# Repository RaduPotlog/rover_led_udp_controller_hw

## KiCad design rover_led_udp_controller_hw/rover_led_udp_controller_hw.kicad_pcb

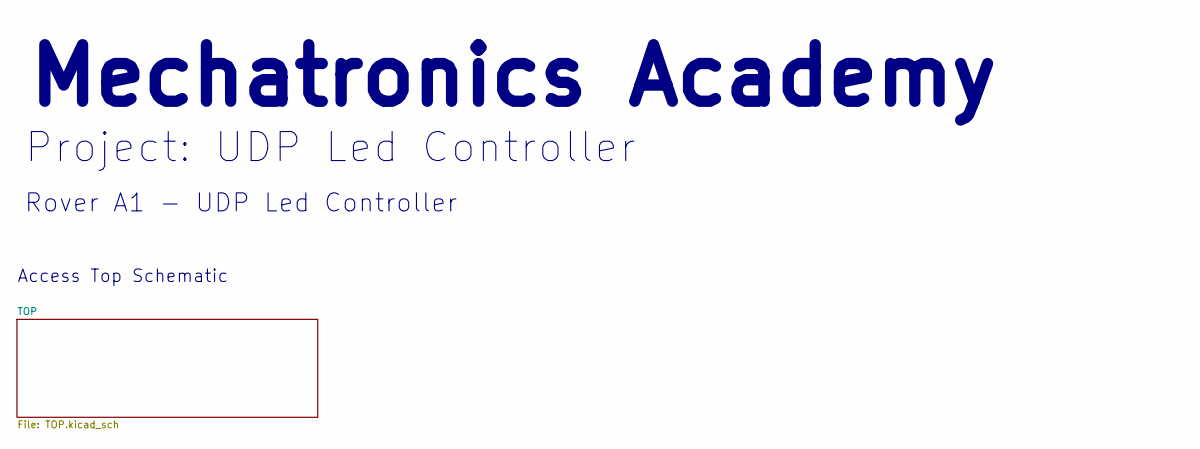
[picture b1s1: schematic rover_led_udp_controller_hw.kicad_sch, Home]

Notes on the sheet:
Rover A1 - UDP Led Controller
Project: UDP Led Controller
Access Top Schematic
Mechatronics Academy

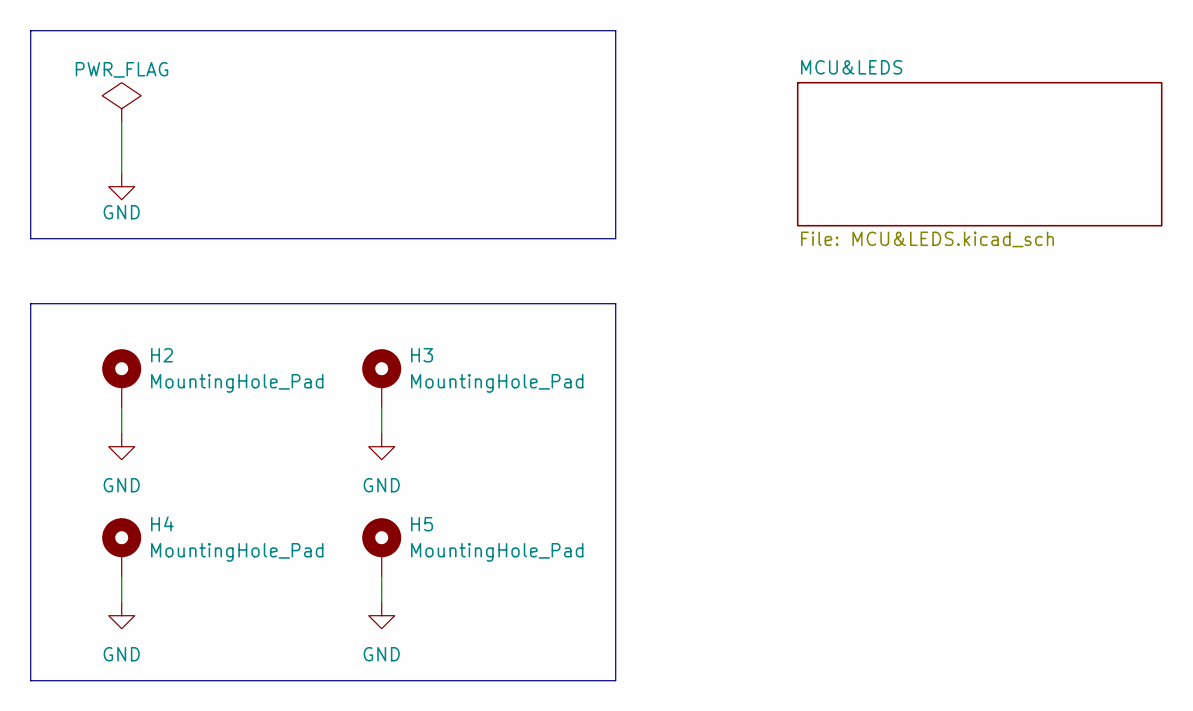
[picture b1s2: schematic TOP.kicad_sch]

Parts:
H2, H3, H4, H5: MountingHole_Pad; MountingHole_2.5mm_Pad_Via

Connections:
GND: H2.1 (1_1), H3.1 (1_1), H4.1 (1_1), H5.1 (1_1); also elsewhere on the board

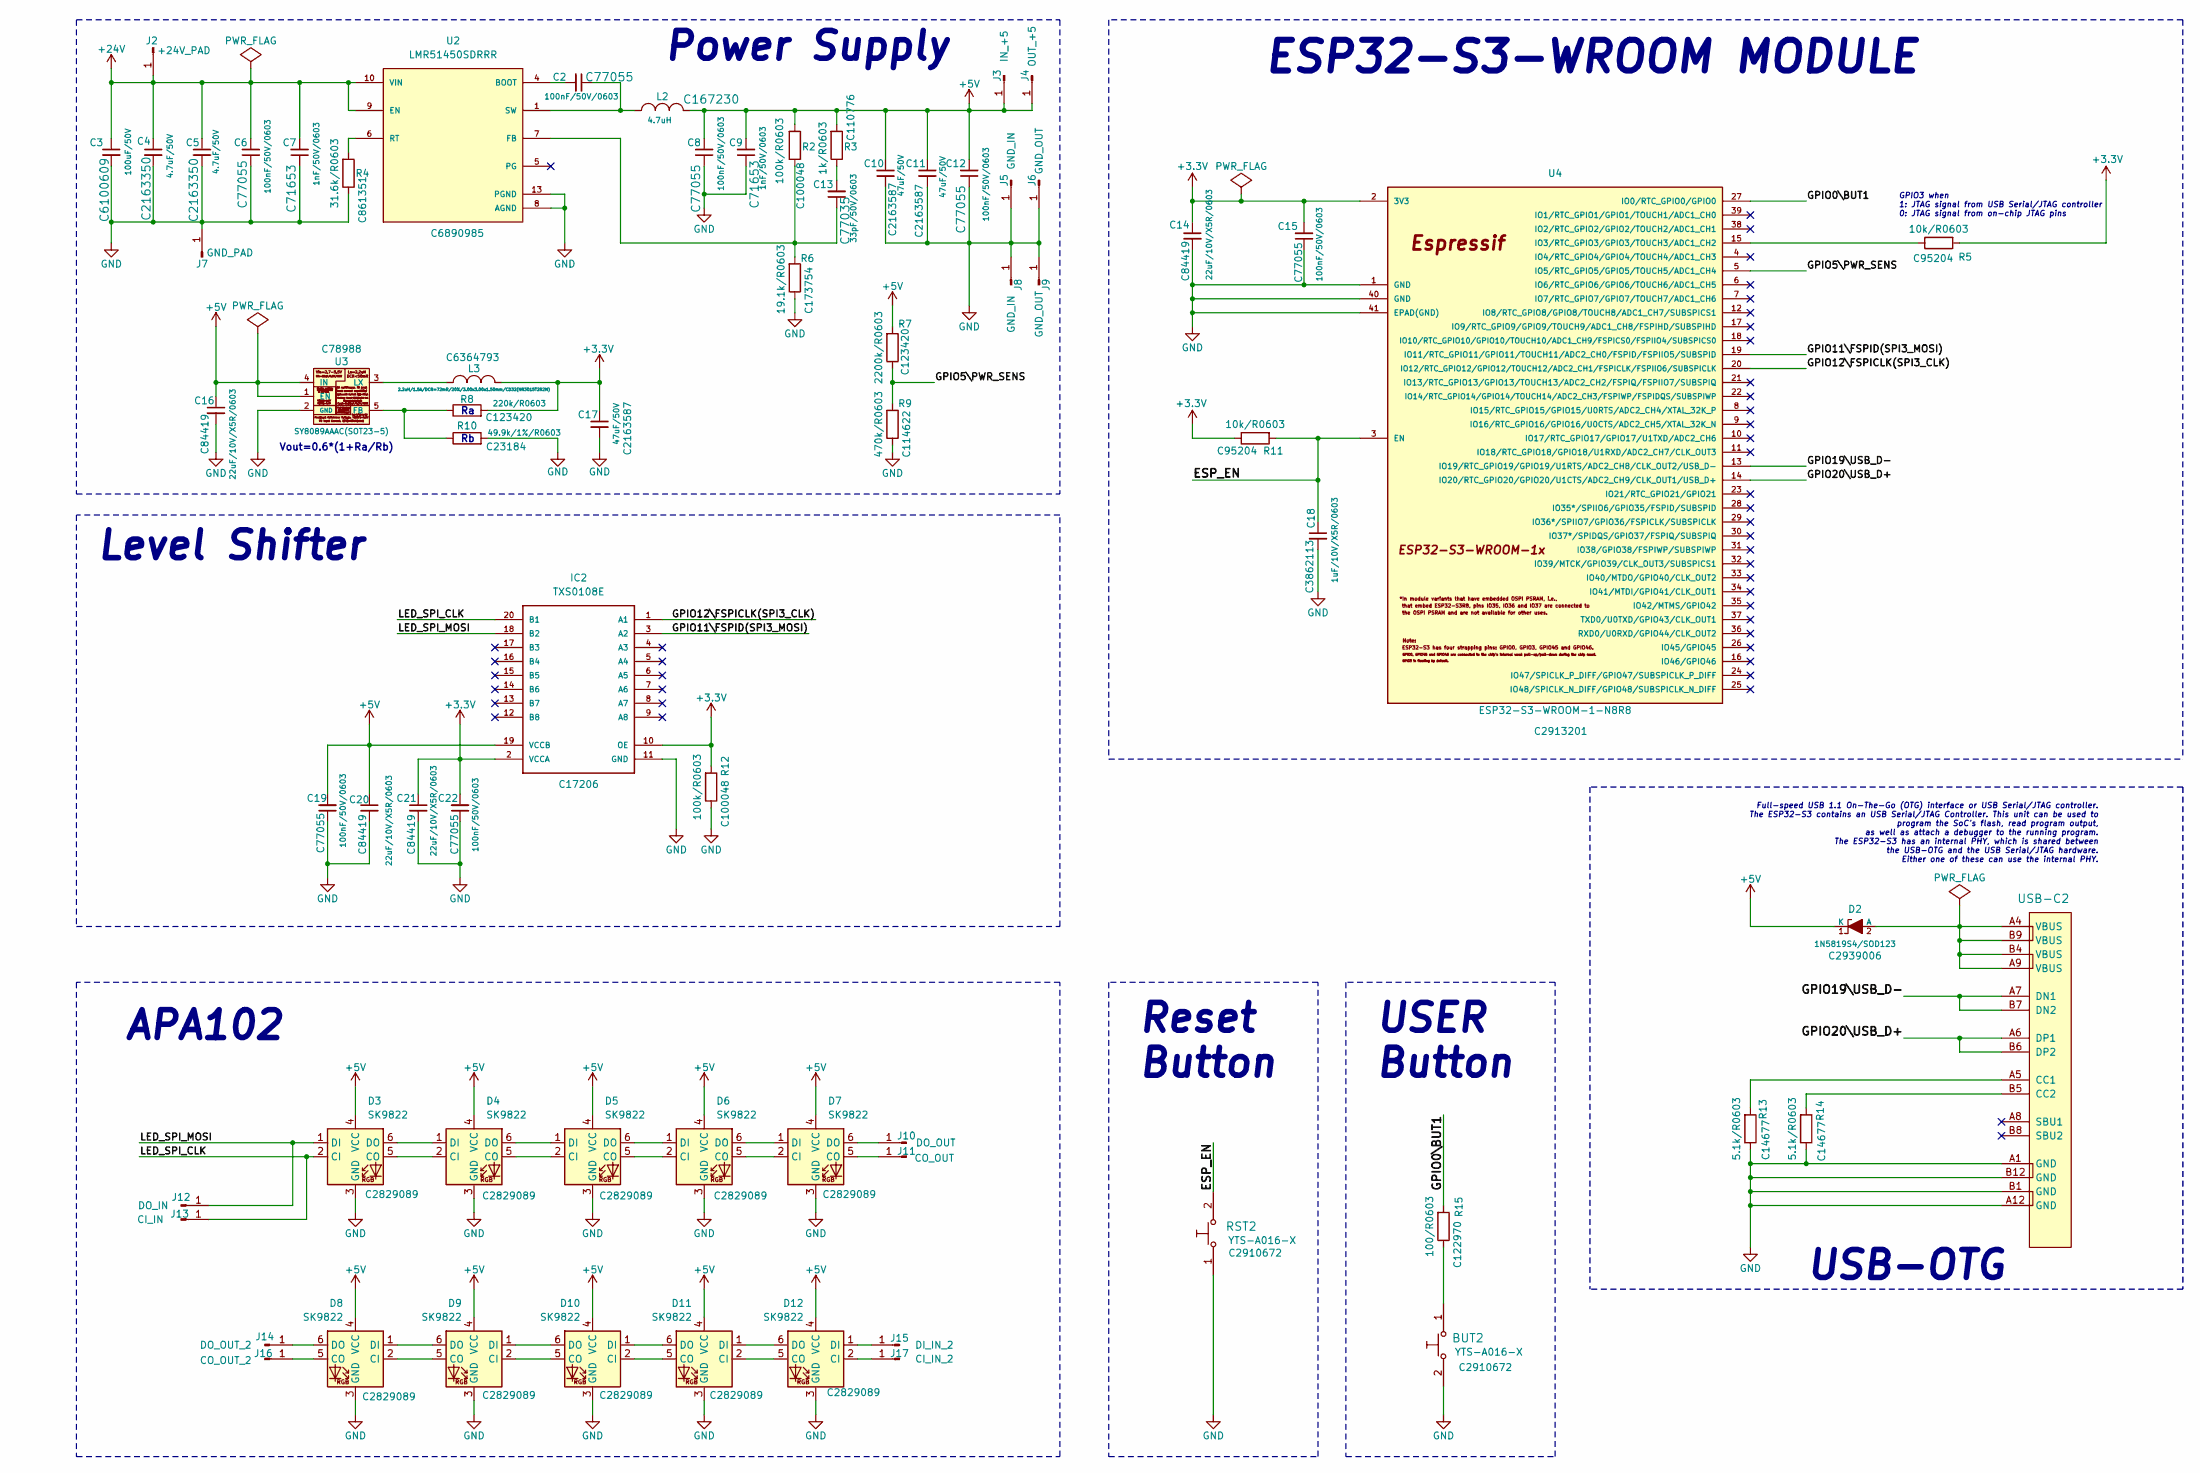
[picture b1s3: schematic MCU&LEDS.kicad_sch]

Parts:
BUT2: YTS-A016-X; JLCPCB C2910672
C2, C6, C8, C12, C15, C19, C22: 100nF/50V/0603; C_0603_1608Metric; JLCPCB C77055
C3: 100uF/50V; CP_Elec_8x10.5; JLCPCB C6100609
C4, C5: 4.7uF/50V; CP_Elec_4x5.7; JLCPCB C2163350
C7, C9: 1nF/50V/0603; C_0603_1608Metric; JLCPCB C71653
C10, C11, C17: 47uF/50V; CP_Elec_6.3x7.7; JLCPCB C2163587
C13: 33pF/50V/0603; C_0603_1608Metric; JLCPCB C77035
C14, C16, C20, C21: 22uF/10V/X5R/0603; C_0603_1608Metric; JLCPCB C84419
C18: 1uF/10V/X5R/0603; C_0603_1608Metric; JLCPCB C3862113
D2: 1N5819S4/SOD123; SOD-123_1C-2A_KA; JLCPCB C2939006
D3, D4, D5, D6, D7, D8, D9, D10, D11, D12: SK9822; LED_RGB_5050-6; JLCPCB C2829089
IC2: TXS0108E; PW_R-PDSO-G20; JLCPCB C17206
J2: +24V_PAD; TestPoint_Pad_1
J3: IN_+5; TestPoint_Pad_1
J4: OUT_+5; TestPoint_Pad_1
J5, J8: GND_IN; TestPoint_Pad_1
J6, J9: GND_OUT; TestPoint_Pad_1
J7: GND_PAD; TestPoint_Pad_1
J10: DO_OUT; TestPoint_Pad
J11: CO_OUT; TestPoint_Pad
J12: DO_IN; TestPoint_Pad
J13: CI_IN; TestPoint_Pad
J14: DO_OUT_2; TestPoint_Pad
J15: DI_IN_2; TestPoint_Pad
J16: CO_OUT_2; TestPoint_Pad
J17: CI_IN_2; TestPoint_Pad
L2: 4.7uH; L_Sunlord_MWSA1003S; JLCPCB C167230
L3: 2.2uH/1.5A/DCR=72mR/20%/3.00x3.00x1.50mm/CD32(NR3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; CD32; JLCPCB C6364793
R2, R12: 100k/R0603; R_0603_1608Metric_Pad0.98x0.95mm_HandSolder; JLCPCB C100048
R3: 1k/R0603; R_0603_1608Metric_Pad0.98x0.95mm_HandSolder; JLCPCB C110776
R4: 31.6k/R0603; R_0603_1608Metric_Pad0.98x0.95mm_HandSolder; JLCPCB C861351
R5, R11: 10k/R0603; R_0603_1608Metric_Pad0.98x0.95mm_HandSolder; JLCPCB C95204
R6: 19.1k/R0603; R_0603_1608Metric_Pad0.98x0.95mm_HandSolder; JLCPCB C173754
R7: 2200k/R0603; R_0603_1608Metric_Pad0.98x0.95mm_HandSolder; JLCPCB C123420
R8: 220k/R0603; R_0603_1608Metric_Pad0.98x0.95mm_HandSolder; JLCPCB C123420
R9: 470k/R0603; R_0603_1608Metric_Pad0.98x0.95mm_HandSolder; JLCPCB C114622
R10: 49.9k/1%/R0603; R_0603_1608Metric_Pad0.98x0.95mm_HandSolder; JLCPCB C23184
R13, R14: 5.1k/R0603; R_0603_1608Metric_Pad0.98x0.95mm_HandSolder; JLCPCB C14677
R15: 100/R0603; R_0603_1608Metric_Pad0.98x0.95mm_HandSolder; JLCPCB C122970
RST2: YTS-A016-X; JLCPCB C2910672
U2: LMR51450SDRRR; PARTREV December 2022; JLCPCB C6890985
U3: SY8089AAAC(SOT23-5); SOT-23-5; JLCPCB C78988
U4: ESP32-S3-WROOM-1-N8R8; ESP32-­S3-­WROOM­-1; JLCPCB C2913201
USB-C2: USB2.0_TYPE-C(A40-00119-A52-12); USB2.0_TYPE-C-ONLY-PADS

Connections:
+3.3V: C14.1, C15.2, C17.1, C21.1, C22.2, IC2.2 (VCCA), IC2.10 (OE), L3.2, R5.2, R8.2, R11.1, R12.2, U4.2 (3V3)
+5V: C8.2, C9.2, C10.1, C11.1, C12.2, C16.1, C19.2, C20.1, D2.1 (K), D3.4 (VCC), D4.4 (VCC), D5.4 (VCC), D6.4 (VCC), D7.4 (VCC), D8.4 (VCC), D9.4 (VCC), D10.4 (VCC), D11.4 (VCC), D12.4 (VCC), IC2.19 (VCCB), J3.1 (Pin_1_1), J4.1 (Pin_1_1), L2.2, R2.2, R3.2, R7.2, U3.1 (EN), U3.4 (IN)
+24V: C3.1, C4.1, C5.1, C6.2, C7.2, J2.1 (Pin_1_1), U2.9 (EN), U2.10 (VIN), U2.11 (VIN), U2.12 (VIN)
/TOP/MCU&LEDS/ESP_EN: C18.1, R11.2, RST2.2, U4.3 (EN)
/TOP/MCU&LEDS/GPIO0\BUT1: R15.2, U4.27 (IO0/RTC_GPIO0/GPIO0)
/TOP/MCU&LEDS/GPIO5\PWR_SENS: R7.1, R9.2, U4.5 (IO5/RTC_GPIO5/GPIO5/TOUCH5/ADC1_CH4)
/TOP/MCU&LEDS/GPIO11\FSPID(SPI3_MOSI): IC2.3 (A2), U4.19 (IO11/RTC_GPIO11/GPIO11/TOUCH11/ADC2_CH0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)
/TOP/MCU&LEDS/GPIO12\FSPICLK(SPI3_CLK): IC2.1 (A1), U4.20 (IO12/RTC_GPIO12/GPIO12/TOUCH12/ADC2_CH1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)
/TOP/MCU&LEDS/GPIO19\USB_D-: U4.13 (IO19/RTC_GPIO19/GPIO19/U1RTS/ADC2_CH8/C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), USB-C2.A7 (DN1), USB-C2.B7 (DN2)
/TOP/MCU&LEDS/GPIO20\USB_D+: U4.14 (IO20/RTC_GPIO20/GPIO20/U1CTS/ADC2_CH9/C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), USB-C2.A6 (DP1), USB-C2.B6 (DP2)
/TOP/MCU&LEDS/LED_SPI_CLK: D3.2 (CI), IC2.20 (B1), J13.1 (Pin_1_1)
/TOP/MCU&LEDS/LED_SPI_MOSI: D3.1 (DI), IC2.18 (B2), J12.1 (Pin_1_1)
GND: BUT2.2, C3.2, C4.2, C5.2, C6.1, C7.1, C8.1, C9.1, C10.2, C11.2, C12.1, C14.2, C15.1, C16.2, C17.2, C18.2, C19.1, C20.2, C21.2, C22.1, D3.3 (GND), D4.3 (GND), D5.3 (GND), D6.3 (GND), D7.3 (GND), D8.3 (GND), D9.3 (GND), D10.3 (GND), D11.3 (GND), D12.3 (GND), IC2.11 (GND), J5.1 (Pin_1_1), J6.1 (Pin_1_1), J7.1 (Pin_1_1), J8.1 (Pin_1_1), J9.1 (Pin_1_1), R4.1, R6.1, R9.1, R10.2, R12.1, R13.1, R14.1, RST2.1, U2.8 (AGND), U2.13 (PGND), U3.2 (GND), U4.1 (GND), U4.40 (GND), U4.41 (EPAD(GND)), USB-C2.A1 (GND), USB-C2.A12 (GND), USB-C2.B1 (GND), USB-C2.B12 (GND); also elsewhere on the board
unnamed: BUT2.1, R15.1
unnamed: C2.1, L2.1, U2.1 (SW), U2.2 (SW), U2.3 (SW)
unnamed: C13.2, R3.1
unnamed: D2.2 (A), USB-C2.A4 (VBUS), USB-C2.A9 (VBUS), USB-C2.B4 (VBUS), USB-C2.B9 (VBUS)
unnamed: D3.5 (CO), D4.2 (CI)
unnamed: D3.6 (DO), D4.1 (DI)
unnamed: D4.5 (CO), D5.2 (CI)
unnamed: D4.6 (DO), D5.1 (DI)
unnamed: D5.5 (CO), D6.2 (CI)
unnamed: D5.6 (DO), D6.1 (DI)
unnamed: D6.5 (CO), D7.2 (CI)
unnamed: D6.6 (DO), D7.1 (DI)
unnamed: D7.5 (CO), J11.1 (Pin_1_1)
unnamed: D7.6 (DO), J10.1 (Pin_1_1)
unnamed: D8.2 (CI), D9.5 (CO)
unnamed: D8.5 (CO), J16.1 (Pin_1_1)
unnamed: D8.1 (DI), D9.6 (DO)
unnamed: D8.6 (DO), J14.1 (Pin_1_1)
unnamed: D10.2 (CI), D11.5 (CO)
unnamed: D9.2 (CI), D10.5 (CO)
unnamed: D10.1 (DI), D11.6 (DO)
unnamed: D9.1 (DI), D10.6 (DO)
unnamed: D11.2 (CI), D12.5 (CO)
unnamed: D11.1 (DI), D12.6 (DO)
unnamed: D12.2 (CI), J17.1 (Pin_1_1)
unnamed: D12.1 (DI), J15.1 (Pin_1_1)
unnamed: C2.2, U2.4 (BOOT)
unnamed: C13.1, R2.1, R6.2, U2.7 (FB)
unnamed: R4.2, U2.6 (RT)
unnamed: R8.1, R10.1, U3.5 (FB)
unnamed: L3.1, U3.3 (LX)
unnamed: R5.1, U4.15 (IO3/RTC_GPIO3/GPIO3/TOUCH3/ADC1_CH2)
unnamed: R13.2, USB-C2.A5 (CC1)
unnamed: R14.2, USB-C2.B5 (CC2)

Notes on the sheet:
ESP32-S3-WROOM MODULE
Power Supply
Full-speed USB 1.1 On-The-Go (OTG) interface or USB Serial/JTAG controller. The ESP32-S3 contains an USB Serial/JTAG Controller. This unit can be used to program the SoC’s flash, read program output, as well as attach a debugger to the running program. The ESP32-S3 has an internal PHY, which is sha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
Vout=0.6*(1+Ra/Rb)
GPIO3 when 1: JTAG signal from USB Serial/JTAG controller 0: JTAG signal from on-chip JTAG pins
Reset Button
USB-OTG
Level Shifter
APA102
USER Button

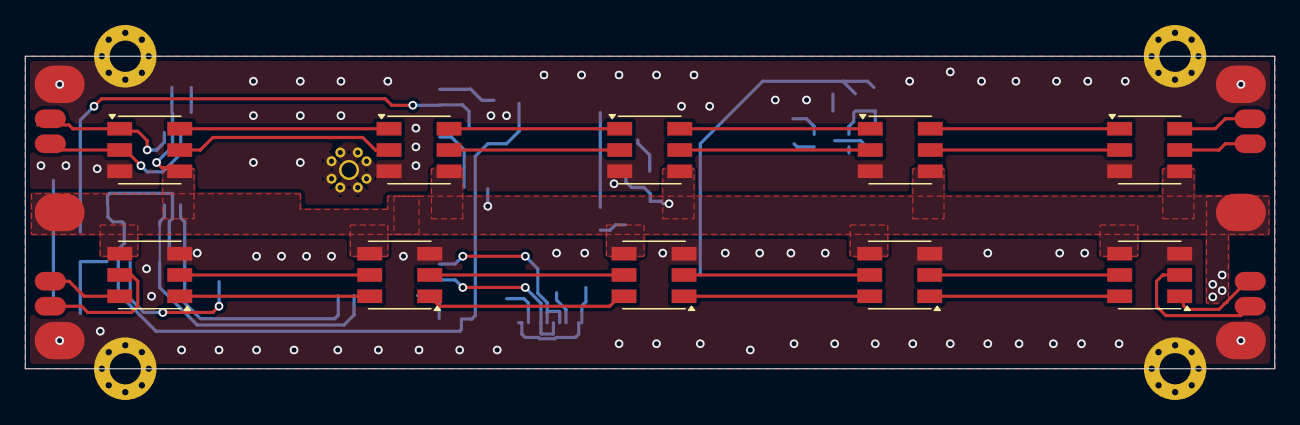
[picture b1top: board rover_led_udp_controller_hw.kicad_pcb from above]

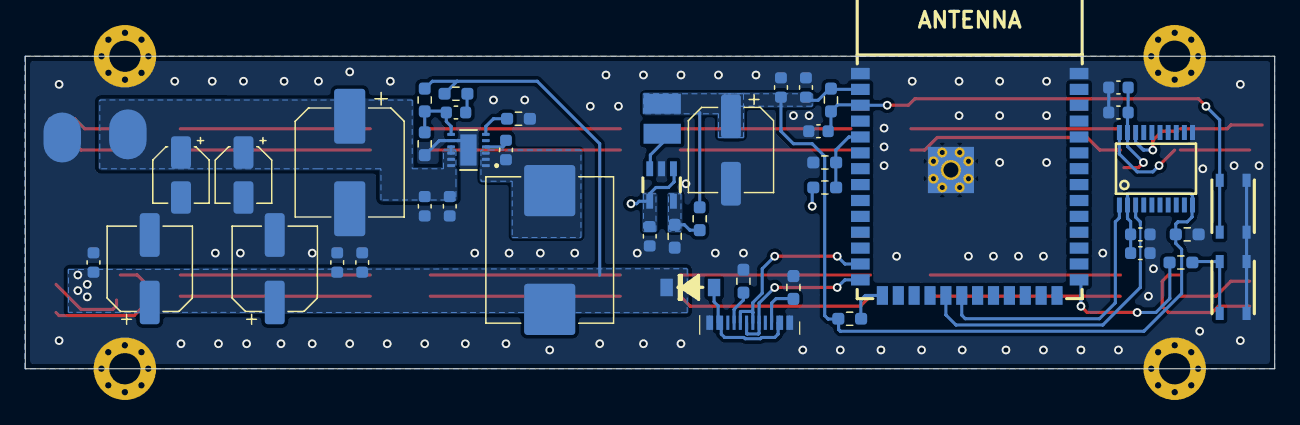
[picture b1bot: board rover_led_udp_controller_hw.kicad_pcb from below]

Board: 2 copper layers, 100.0 x 25.0 mm, 75 parts (47 on the bottom side), 47 nets.

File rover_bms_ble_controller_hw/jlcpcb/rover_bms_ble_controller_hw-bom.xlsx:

Comment | Designator | Footprint | JLCPCB Part #（optional）
YTS-A016-X | BUT2,RST2 | OLIMEX_Buttons-FP:YTS-A016-X | C2910672
100nF/50V/0603 | C2,C6,C8,C12,C15,C19,C22 | Capacitor_SMD:C_0603_1608Metric | C77055
100uF/50V | C3 | Capacitor_SMD:CP_Elec_8x10.5 | C6100609
4.7uF/50V | C4,C5 | Capacitor_SMD:CP_Elec_4x5.7 | C2163350
1nF/50V/0603 | C7,C9 | Capacitor_SMD:C_0603_1608Metric | C71653
47uF/50V | C10,C11,C17 | Capacitor_SMD:CP_Elec_6.3x7.7 | C2163587
33pF/50V/0603 | C13 | Capacitor_SMD:C_0603_1608Metric | C77035
22uF/10V/X5R/0603 | C14,C16,C20,C21 | Capacitor_SMD:C_0603_1608Metric | C84419
1uF/10V/X5R/0603 | C18 | Capacitor_SMD:C_0603_1608Metric | C3862113
1N5819S4/SOD123 | D2 | OLIMEX_Diodes-FP:SOD-123_1C-2A_KA | C2939006
SK9822 | D3,D4,D5,D6,D7,D8,D9,D10,D11,D12 | LED_SMD:LED_RGB_5050-6 | C2829089,C2829089
TXS0108E | IC2 | MechatronicsAcademy:PW_R-PDSO-G20 | C17206
4.7uH | L2 | Inductor_SMD:L_Sunlord_MWSA1003S | C167230
2.2uH/1.5A/DCR=72mR/20%/3.00x3.00x1.50mm/CD32(NR3015T2R2M) | L3 | OLIMEX_RLC-FP:CD32 | C6364793
100k/R0603 | R2,R12 | Resistor_SMD:R_0603_1608Metric_Pad0.98x0.95mm_HandSolder | C100048
1k/R0603 | R3 | Resistor_SMD:R_0603_1608Metric_Pad0.98x0.95mm_HandSolder | C110776
31.6k/R0603 | R4 | Resistor_SMD:R_0603_1608Metric_Pad0.98x0.95mm_HandSolder | C861351
10k/R0603 | R5,R11 | Resistor_SMD:R_0603_1608Metric_Pad0.98x0.95mm_HandSolder | C95204
19.1k/R0603 | R6 | Resistor_SMD:R_0603_1608Metric_Pad0.98x0.95mm_HandSolder | C173754
2200k/R0603 | R7 | Resistor_SMD:R_0603_1608Metric_Pad0.98x0.95mm_HandSolder | C123420
220k/R0603 | R8 | Resistor_SMD:R_0603_1608Metric_Pad0.98x0.95mm_HandSolder | C123420
470k/R0603 | R9 | Resistor_SMD:R_0603_1608Metric_Pad0.98x0.95mm_HandSolder | C114622
49.9k/1%/R0603 | R10 | Resistor_SMD:R_0603_1608Metric_Pad0.98x0.95mm_HandSolder | C23184
5.1k/R0603 | R13,R14 | Resistor_SMD:R_0603_1608Metric_Pad0.98x0.95mm_HandSolder | C14677
100/R0603 | R15 | Resistor_SMD:R_0603_1608Metric_Pad0.98x0.95mm_HandSolder | C122970
LMR51450SDRRR | U2 | MechatronicsAcademy:LMR51450SDRRR | C6890985
SY8089AAAC(SOT23-5) | U3 | OLIMEX_Regulators-FP:SOT-23-5 | C78988
ESP32-S3-WROOM-1-N8R8 | U4 | OLIMEX_Cases-FP:ESP32-S3-WROOM-1 | C2913201

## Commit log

2026-06-23 Final version
2026-06-26 Rename project
